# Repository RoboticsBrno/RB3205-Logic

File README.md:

# About Logic

Logic is a universal programmable toy designed for teaching programming
developed at [Robotárna](https://helceletka.cz/robotarna).

Logic resembles a game console. It has 105 RGB LEDs that can serve as a display, it
has numerous buttons and a buzzer. Under the hood, it is powered by the ESP32
microcontroller.

Kids (well, not only them) can create custom games and
learn programming while doing so. It is even possible to run multiplayer games as the on-board
processor features both, WiFi and Bluetooth 4.

This project was prepared for [Robotic Camp 2021](https://2021.robotickytabor.cz/) ­–
the page is available, however, in Czech. You will find more project there. You
can also see our [GitHub](https://github.com/RoboticsBrno) for find out more
about our other projects.

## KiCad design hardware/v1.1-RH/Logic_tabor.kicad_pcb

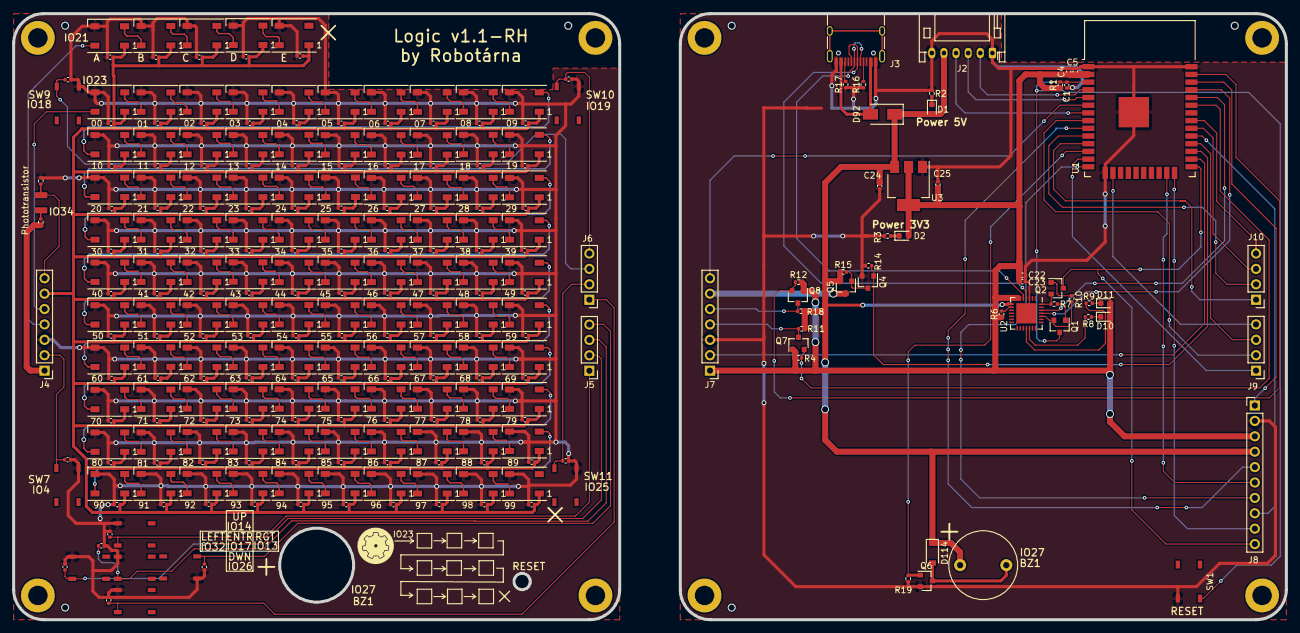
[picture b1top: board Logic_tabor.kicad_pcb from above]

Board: 2 copper layers, 100.0 x 100.0 mm, 294 parts (1 on the bottom side), 170 nets.

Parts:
B1, B2: Board
BZ1: Buzzer; PIEZO
C1: 1u; C_0402_1005Metric
C2, C3, C5, C6, C7, C8, C9, C10, C15, C16, C21, C23, C31, C32, C33, C34, C35, C36, C37, C38, C39, C40, C41, C42, C43, C44, C45, C46, C47, C48, C49, C50, C51, C52, C53, C54, C55, C56, C57, C58, C59, C60, C61, C62, C63, C64, C65, C66, C67, C68, C69, C70, C71, C72, C73, C74, C75, C76, C77, C78, C79, C80, C81, C82, C83, C84, C85, C86, C87, C88, C89, C90, C91, C92, C93, C94, C95, C96, C97, C98, C99, C100, C101, C102, C103, C104, C105, C106, C107, C108, C109, C110, C111, C112, C113, C114, C115, C116, C117, C118, C119, C120, C121, C122, C123, C124, C125: 100n; C_0402_1005Metric
C4, C22, C24, C25: 10u; C_0402_1005Metric
C11, C12, C13, C14, C17, C18, C19, C20, C126: 10n; C_0402_1005Metric
D1, D2, D10, D11: green; LED_0603_1608Metric
D3, D4, D5, D6, D12, D13, D14, D15, D16, D17, D18, D19, D20, D21, D22, D23, D24, D25, D26, D27, D28, D29, D30, D31, D32, D33, D34, D35, D36, D37, D38, D39, D40, D41, D42, D43, D44, D45, D46, D47, D48, D49, D50, D51, D52, D53, D54, D55, D56, D57, D58, D59, D60, D61, D62, D63, D64, D65, D66, D67, D68, D69, D70, D71, D72, D73, D74, D75, D76, D77, D78, D79, D80, D81, D82, D83, D84, D85, D86, D87, D88, D89, D90, D91, D93, D94, D95, D96, D97, D98, D99, D100, D101, D102, D103, D104, D105, D106, D107, D108, D109, D110, D111, D112, D113: WS2812C; LED_WS2812B_PLCC4_5.0x5.0mm_P3.2mm
D92: DIODE; D_SMA
D114: D_Schottky; D_SOD-123
DRA1, DRA2: Logo_Robotarna; RobotarnaLogo-6mm
H1, H2, H3, H4, H5, H6, H7, H8: MountingHole; MountingHole_3.2mm_M3_DIN965_Pad
J2: Conn_01x06_Male; JST_PH_S6B-PH-K_1x06_P2.00mm_Horizontal
J3: USB_C_Receptacle_USB2.0; USB_C_Receptacle_HRO_TYPE-C-31-M-12
J4: Conn_01x07_Female; PinHeader_1x07_P2.54mm_Vertical
J5, J6: Conn_01x04_Female; PinHeader_1x04_P2.54mm_Vertical
J7: Conn_01x07_Male; PinHeader_1x07_P2.54mm_Vertical
J8: Conn_01x10_Male; PinHeader_1x10_P2.54mm_Vertical
J9, J10: Conn_01x04_Male; PinHeader_1x04_P2.54mm_Vertical
Q1, Q2: Q_NPN_BEC; SOT-23
Q3: Q_Photo_NPN; SMD,3.5x2.8x1.9mm
Q4, Q6, Q7, Q8: Q_NMOS_GSD; SOT-23
Q5: Q_PMOS_GSD; SOT-23
R1, R2, R3, R4, R6, R7, R8, R9, R10, R11, R12, R13, R18: 10k; R_0402_1005Metric
R5: 22k; R_0402_1005Metric
R14, R15, R19: 100k; R_0402_1005Metric
R16, R17: 5k1; R_0402_1005Metric
SW1, SW2, SW3, SW4, SW5, SW7, SW8, SW9, SW10, SW11: button; Tactile_switch
U1: ESP32-WROOM-32
U2: CP2102N-A01-GQFN28; QFN-28-1EP_5x5mm_P0.5mm_EP3.35x3.35mm
U3: AMS1117-3.3; SOT-223-3_TabPin2

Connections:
5V: BZ1.1 (-), C24.1, D1.2 (A), D92.1 (K), D114.1 (K), J2.5, J8.4, Q5.2 (S), R11.1, R15.1, R18.1, U2.8 (VBUS), U3.3 (VI)
/elektronika.sch/3V3: C4.2, C5.2, C22.2, C23.2, C25.1, D2.2 (A), D10.2 (A), D11.2 (A), J7.1, J8.3, Q7.1 (G), Q8.1 (G), R1.1, R4.1, R6.1, R12.1, U1.2 (VDD), U2.6 (VDD), U2.7 (REGIN), U3.2 (VO)
/elektronika.sch/DATA_HERNI_LED: J7.5, Q8.3 (D), R18.2
/elektronika.sch/DATA_ZADANI_LED: J7.4, Q7.3 (D), R11.2
/elektronika.sch/GND: C1.2, C4.1, C5.1, C22.1, C23.1, C24.2, C25.2, J2.1, J2.6, J3.A1 (GND), J3.A12 (GND), J3.B1 (GND), J3.B12 (GND), J7.3, J8.2, Q4.2 (S), Q6.2 (S), R2.1, R3.1, R14.2, R16.1, R17.1, R19.1, SW1.2, U1.1 (GND), U1.15 (GND), U1.38 (GND), U1.39 (GND), U2.3 (GND), U2.29 (GND), U3.1 (GND)
/elektronika.sch/SENZOR_SVETLA: J7.7, U1.6 (IO34)
/elektronika.sch/SW_2: J9.3, U1.28 (IO17)
/elektronika.sch/SW_3: J9.4, U1.16 (IO13)
/elektronika.sch/SW_4: J9.2, U1.8 (IO32)
/elektronika.sch/SW_5: J9.1, U1.13 (IO14)
/elektronika.sch/SW_7: J7.2, U1.26 (IO4)
/elektronika.sch/SW_8: J10.1, U1.11 (IO26)
/elektronika.sch/SW_9: J10.3, U1.30 (IO18)
/elektronika.sch/SW_10: J10.4, U1.31 (IO19)
/elektronika.sch/SW_11: J10.2, U1.10 (IO25)
/elektronika.sch/V_LED_1: J7.6, Q5.3 (D)
/ovladaci_prvky.sch/3V3: J4.1, R5.1
/ovladaci_prvky.sch/DATA_HERNI_LED: D12.4 (DIN), J4.5
/ovladaci_prvky.sch/DATA_ZADANI_LED: D3.4 (DIN), J4.4
/ovladaci_prvky.sch/GND: C2.2, C3.2, C6.2, C7.2, C8.2, C9.2, C10.2, C11.1, C12.1, C13.1, C14.1, C15.2, C16.2, C17.1, C18.1, C19.1, C20.1, C21.2, C31.2, C32.2, C33.2, C34.2, C35.2, C36.2, C37.2, C38.2, C39.2, C40.2, C41.2, C42.2, C43.2, C44.2, C45.2, C46.2, C47.2, C48.2, C49.2, C50.2, C51.2, C52.2, C53.2, C54.2, C55.2, C56.2, C57.2, C58.2, C59.2, C60.2, C61.2, C62.2, C63.2, C64.2, C65.2, C66.2, C67.2, C68.2, C69.2, C70.2, C71.2, C72.2, C73.2, C74.2, C75.2, C76.2, C77.2, C78.2, C79.2, C80.2, C81.2, C82.2, C83.2, C84.2, C85.2, C86.2, C87.2, C88.2, C89.2, C90.2, C91.2, C92.2, C93.2, C94.2, C95.2, C96.2, C97.2, C98.2, C99.2, C100.2, C101.2, C102.2, C103.2, C104.2, C105.2, C106.2, C107.2, C108.2, C109.2, C110.2, C111.2, C112.2, C113.2, C114.2, C115.2, C116.2, C117.2, C118.2, C119.2, C120.2, C121.2, C122.2, C123.2, C124.2, C125.2, C126.1, D3.3 (VSS), D4.3 (VSS), D5.3 (VSS), D6.3 (VSS), D12.3 (VSS), D13.3 (VSS), D14.3 (VSS), D15.3 (VSS), D16.3 (VSS), D17.3 (VSS), D18.3 (VSS), D19.3 (VSS), D20.3 (VSS), D21.3 (VSS), D22.3 (VSS), D23.3 (VSS), D24.3 (VSS), D25.3 (VSS), D26.3 (VSS), D27.3 (VSS), D28.3 (VSS), D29.3 (VSS), D30.3 (VSS), D31.3 (VSS), D32.3 (VSS), D33.3 (VSS), D34.3 (VSS), D35.3 (VSS), D36.3 (VSS), D37.3 (VSS), D38.3 (VSS), D39.3 (VSS), D40.3 (VSS), D41.3 (VSS), D42.3 (VSS), D43.3 (VSS), D44.3 (VSS), D45.3 (VSS), D46.3 (VSS), D47.3 (VSS), D48.3 (VSS), D49.3 (VSS), D50.3 (VSS), D51.3 (VSS), D52.3 (VSS), D53.3 (VSS), D54.3 (VSS), D55.3 (VSS), D56.3 (VSS), D57.3 (VSS), D58.3 (VSS), D59.3 (VSS), D60.3 (VSS), D61.3 (VSS), D62.3 (VSS), D63.3 (VSS), D64.3 (VSS), D65.3 (VSS), D66.3 (VSS), D67.3 (VSS), D68.3 (VSS), D69.3 (VSS), D70.3 (VSS), D71.3 (VSS), D72.3 (VSS), D73.3 (VSS), D74.3 (VSS), D75.3 (VSS), D76.3 (VSS), D77.3 (VSS), D78.3 (VSS), D79.3 (VSS), D80.3 (VSS), D81.3 (VSS), D82.3 (VSS), D83.3 (VSS), D84.3 (VSS), D85.3 (VSS), D86.3 (VSS), D87.3 (VSS), D88.3 (VSS), D89.3 (VSS), D90.3 (VSS), D91.3 (VSS), D93.3 (VSS), D94.3 (VSS), D95.3 (VSS), D96.3 (VSS), D97.3 (VSS), D98.3 (VSS), D99.3 (VSS), D100.3 (VSS), D101.3 (VSS), D102.3 (VSS), D103.3 (VSS), D104.3 (VSS), D105.3 (VSS), D106.3 (VSS), D107.3 (VSS), D108.3 (VSS), D109.3 (VSS), D110.3 (VSS), D111.3 (VSS), D112.3 (VSS), D113.3 (VSS), J4.3, R13.2, SW2.2, SW3.2, SW4.2, SW5.2, SW7.2, SW8.2, SW9.2, SW10.2, SW11.2
/ovladaci_prvky.sch/SENZOR_SVETLA: J4.7, Q3.2 (E), R13.1
/ovladaci_prvky.sch/SW_2: C11.2, J5.3, SW2.1
/ovladaci_prvky.sch/SW_3: C12.2, J5.4, SW3.1
/ovladaci_prvky.sch/SW_4: C13.2, J5.2, SW4.1
/ovladaci_prvky.sch/SW_5: C14.2, J5.1, SW5.1
/ovladaci_prvky.sch/SW_7: C126.2, J4.2, SW7.1
/ovladaci_prvky.sch/SW_8: C17.2, J6.1, SW8.1
/ovladaci_prvky.sch/SW_9: C18.2, J6.3, SW9.1
/ovladaci_prvky.sch/SW_10: C19.2, J6.4, SW10.1
/ovladaci_prvky.sch/SW_11: C20.2, J6.2, SW11.1
/ovladaci_prvky.sch/V_LED_1: C2.1, C3.1, C6.1, C7.1, C8.1, C9.1, C10.1, C15.1, C16.1, C21.1, C31.1, C32.1, C33.1, C34.1, C35.1, C36.1, C37.1, C38.1, C39.1, C40.1, C41.1, C42.1, C43.1, C44.1, C45.1, C46.1, C47.1, C48.1, C49.1, C50.1, C51.1, C52.1, C53.1, C54.1, C55.1, C56.1, C57.1, C58.1, C59.1, C60.1, C61.1, C62.1, C63.1, C64.1, C65.1, C66.1, C67.1, C68.1, C69.1, C70.1, C71.1, C72.1, C73.1, C74.1, C75.1, C76.1, C77.1, C78.1, C79.1, C80.1, C81.1, C82.1, C83.1, C84.1, C85.1, C86.1, C87.1, C88.1, C89.1, C90.1, C91.1, C92.1, C93.1, C94.1, C95.1, C96.1, C97.1, C98.1, C99.1, C100.1, C101.1, C102.1, C103.1, C104.1, C105.1, C106.1, C107.1, C108.1, C109.1, C110.1, C111.1, C112.1, C113.1, C114.1, C115.1, C116.1, C117.1, C118.1, C119.1, C120.1, C121.1, C122.1, C123.1, C124.1, C125.1, D3.1 (VDD), D4.1 (VDD), D5.1 (VDD), D6.1 (VDD), D12.1 (VDD), D13.1 (VDD), D14.1 (VDD), D15.1 (VDD), D16.1 (VDD), D17.1 (VDD), D18.1 (VDD), D19.1 (VDD), D20.1 (VDD), D21.1 (VDD), D22.1 (VDD), D23.1 (VDD), D24.1 (VDD), D25.1 (VDD), D26.1 (VDD), D27.1 (VDD), D28.1 (VDD), D29.1 (VDD), D30.1 (VDD), D31.1 (VDD), D32.1 (VDD), D33.1 (VDD), D34.1 (VDD), D35.1 (VDD), D36.1 (VDD), D37.1 (VDD), D38.1 (VDD), D39.1 (VDD), D40.1 (VDD), D41.1 (VDD), D42.1 (VDD), D43.1 (VDD), D44.1 (VDD), D45.1 (VDD), D46.1 (VDD), D47.1 (VDD), D48.1 (VDD), D49.1 (VDD), D50.1 (VDD), D51.1 (VDD), D52.1 (VDD), D53.1 (VDD), D54.1 (VDD), D55.1 (VDD), D56.1 (VDD), D57.1 (VDD), D58.1 (VDD), D59.1 (VDD), D60.1 (VDD), D61.1 (VDD), D62.1 (VDD), D63.1 (VDD), D64.1 (VDD), D65.1 (VDD), D66.1 (VDD), D67.1 (VDD), D68.1 (VDD), D69.1 (VDD), D70.1 (VDD), D71.1 (VDD), D72.1 (VDD), D73.1 (VDD), D74.1 (VDD), D75.1 (VDD), D76.1 (VDD), D77.1 (VDD), D78.1 (VDD), D79.1 (VDD), D80.1 (VDD), D81.1 (VDD), D82.1 (VDD), D83.1 (VDD), D84.1 (VDD), D85.1 (VDD), D86.1 (VDD), D87.1 (VDD), D88.1 (VDD), D89.1 (VDD), D90.1 (VDD), D91.1 (VDD), D93.1 (VDD), D94.1 (VDD), D95.1 (VDD), D96.1 (VDD), D97.1 (VDD), D98.1 (VDD), D99.1 (VDD), D100.1 (VDD), D101.1 (VDD), D102.1 (VDD), D103.1 (VDD), D104.1 (VDD), D105.1 (VDD), D106.1 (VDD), D107.1 (VDD), D108.1 (VDD), D109.1 (VDD), D110.1 (VDD), D111.1 (VDD), D112.1 (VDD), D113.1 (VDD), J4.6
/ovladaci_prvky.sch/herni_pole_LED.sch/1.sch/DATA_OUT: D16.2 (DOUT), D17.4 (DIN)
/ovladaci_prvky.sch/herni_pole_LED.sch/2.sch/DATA_OUT: D21.2 (DOUT), D22.4 (DIN)
/ovladaci_prvky.sch/herni_pole_LED.sch/3.sch/DATA_OUT: D26.2 (DOUT), D27.4 (DIN)
/ovladaci_prvky.sch/herni_pole_LED.sch/4.sch/DATA_OUT: D31.2 (DOUT), D32.4 (DIN)
/ovladaci_prvky.sch/herni_pole_LED.sch/5.sch/DATA_OUT: D36.2 (DOUT), D37.4 (DIN)
/ovladaci_prvky.sch/herni_pole_LED.sch/6.sch/DATA_OUT: D41.2 (DOUT), D42.4 (DIN)
/ovladaci_prvky.sch/herni_pole_LED.sch/7.sch/DATA_OUT: D46.2 (DOUT), D47.4 (DIN)
/ovladaci_prvky.sch/herni_pole_LED.sch/8.sch/DATA_OUT: D51.2 (DOUT), D52.4 (DIN)
/ovladaci_prvky.sch/herni_pole_LED.sch/10.sch/DATA_IN: D56.2 (DOUT), D57.4 (DIN)
/ovladaci_prvky.sch/herni_pole_LED.sch/10.sch/DATA_OUT: D61.2 (DOUT), D62.4 (DIN)
/ovladaci_prvky.sch/herni_pole_LED.sch/11.sch/DATA_OUT: D66.2 (DOUT), D67.4 (DIN)
/ovladaci_prvky.sch/herni_pole_LED.sch/12.sch/DATA_OUT: D71.2 (DOUT), D72.4 (DIN)
/ovladaci_prvky.sch/herni_pole_LED.sch/13.sch/DATA_OUT: D76.2 (DOUT), D77.4 (DIN)
/ovladaci_prvky.sch/herni_pole_LED.sch/14.sch/DATA_OUT: D81.2 (DOUT), D82.4 (DIN)
/ovladaci_prvky.sch/herni_pole_LED.sch/15.sch/DATA_OUT: D86.2 (DOUT), D87.4 (DIN)
/ovladaci_prvky.sch/herni_pole_LED.sch/16.sch/DATA_OUT: D91.2 (DOUT), D93.4 (DIN)
/ovladaci_prvky.sch/herni_pole_LED.sch/17.sch/DATA_OUT: D97.2 (DOUT), D98.4 (DIN)
/ovladaci_prvky.sch/herni_pole_LED.sch/18.sch/DATA_OUT: D102.2 (DOUT), D103.4 (DIN)
/ovladaci_prvky.sch/herni_pole_LED.sch/19.sch/DATA_OUT: D107.2 (DOUT), D108.4 (DIN)
DATA_HERNI_LED_LS: Q8.2 (S), R12.2, U1.37 (IO23)
DATA_ZADANI_LED_LS: Q7.2 (S), R4.2, U1.33 (IO21)
EN: C1.1, Q1.3 (C), R1.2, SW1.1, U1.3 (EN)
IO0: J8.10, Q2.3 (C), U1.25 (IO0)
IO2: J8.9, U1.24 (IO2)
IO5: J8.8, U1.29 (IO5)
IO12: J8.7, U1.14 (IO12)
IO15: J8.6, U1.23 (IO15)
IO22: J8.1, U1.36 (IO22)
IO33: J8.5, U1.9 (IO33)
unnamed: BZ1.2 (+), D114.2 (A), Q6.3 (D)
unnamed: D1.1 (K), R2.2
unnamed: D2.1 (K), R3.2
unnamed: D3.2 (DOUT), D4.4 (DIN)
unnamed: D4.2 (DOUT), D5.4 (DIN)
unnamed: D5.2 (DOUT), D6.4 (DIN)
unnamed: D10.1 (K), R8.1
unnamed: D11.1 (K), R9.1
unnamed: D12.2 (DOUT), D13.4 (DIN)
unnamed: D13.2 (DOUT), D14.4 (DIN)
unnamed: D14.2 (DOUT), D15.4 (DIN)
unnamed: D15.2 (DOUT), D16.4 (DIN)
unnamed: D17.2 (DOUT), D18.4 (DIN)
unnamed: D18.2 (DOUT), D19.4 (DIN)
unnamed: D19.2 (DOUT), D20.4 (DIN)
unnamed: D20.2 (DOUT), D21.4 (DIN)
unnamed: D22.2 (DOUT), D23.4 (DIN)
unnamed: D23.2 (DOUT), D24.4 (DIN)
unnamed: D24.2 (DOUT), D25.4 (DIN)
unnamed: D25.2 (DOUT), D26.4 (DIN)
unnamed: D27.2 (DOUT), D28.4 (DIN)
unnamed: D28.2 (DOUT), D29.4 (DIN)
unnamed: D29.2 (DOUT), D30.4 (DIN)
unnamed: D30.2 (DOUT), D31.4 (DIN)
unnamed: D32.2 (DOUT), D33.4 (DIN)
unnamed: D33.2 (DOUT), D34.4 (DIN)
unnamed: D34.2 (DOUT), D35.4 (DIN)
unnamed: D35.2 (DOUT), D36.4 (DIN)
unnamed: D37.2 (DOUT), D38.4 (DIN)
unnamed: D38.2 (DOUT), D39.4 (DIN)
unnamed: D39.2 (DOUT), D40.4 (DIN)
unnamed: D40.2 (DOUT), D41.4 (DIN)
unnamed: D42.2 (DOUT), D43.4 (DIN)
unnamed: D43.2 (DOUT), D44.4 (DIN)
unnamed: D44.2 (DOUT), D45.4 (DIN)
unnamed: D45.2 (DOUT), D46.4 (DIN)
unnamed: D47.2 (DOUT), D48.4 (DIN)
unnamed: D48.2 (DOUT), D49.4 (DIN)
unnamed: D49.2 (DOUT), D50.4 (DIN)
unnamed: D50.2 (DOUT), D51.4 (DIN)
unnamed: D52.2 (DOUT), D53.4 (DIN)
unnamed: D53.2 (DOUT), D54.4 (DIN)
unnamed: D54.2 (DOUT), D55.4 (DIN)
unnamed: D55.2 (DOUT), D56.4 (DIN)
unnamed: D57.2 (DOUT), D58.4 (DIN)
unnamed: D58.2 (DOUT), D59.4 (DIN)
unnamed: D59.2 (DOUT), D60.4 (DIN)
unnamed: D60.2 (DOUT), D61.4 (DIN)
unnamed: D62.2 (DOUT), D63.4 (DIN)
unnamed: D63.2 (DOUT), D64.4 (DIN)
unnamed: D64.2 (DOUT), D65.4 (DIN)
unnamed: D65.2 (DOUT), D66.4 (DIN)
unnamed: D67.2 (DOUT), D68.4 (DIN)
unnamed: D68.2 (DOUT), D69.4 (DIN)
unnamed: D69.2 (DOUT), D70.4 (DIN)
unnamed: D70.2 (DOUT), D71.4 (DIN)
unnamed: D72.2 (DOUT), D73.4 (DIN)
unnamed: D73.2 (DOUT), D74.4 (DIN)
unnamed: D74.2 (DOUT), D75.4 (DIN)
unnamed: D75.2 (DOUT), D76.4 (DIN)
unnamed: D77.2 (DOUT), D78.4 (DIN)
unnamed: D78.2 (DOUT), D79.4 (DIN)
unnamed: D79.2 (DOUT), D80.4 (DIN)
unnamed: D80.2 (DOUT), D81.4 (DIN)
unnamed: D82.2 (DOUT), D83.4 (DIN)
unnamed: D83.2 (DOUT), D84.4 (DIN)
unnamed: D84.2 (DOUT), D85.4 (DIN)
unnamed: D85.2 (DOUT), D86.4 (DIN)
unnamed: D87.2 (DOUT), D88.4 (DIN)
unnamed: D88.2 (DOUT), D89.4 (DIN)
unnamed: D89.2 (DOUT), D90.4 (DIN)
unnamed: D90.2 (DOUT), D91.4 (DIN)
unnamed: D92.2 (A), J3.A4 (VBUS), J3.A9 (VBUS), J3.B4 (VBUS), J3.B9 (VBUS)
unnamed: D93.2 (DOUT), D94.4 (DIN)
unnamed: D94.2 (DOUT), D95.4 (DIN)
unnamed: D95.2 (DOUT), D96.4 (DIN)
unnamed: D96.2 (DOUT), D97.4 (DIN)
unnamed: D98.2 (DOUT), D99.4 (DIN)
unnamed: D100.2 (DOUT), D101.4 (DIN)
unnamed: D99.2 (DOUT), D100.4 (DIN)
unnamed: D101.2 (DOUT), D102.4 (DIN)
unnamed: D103.2 (DOUT), D104.4 (DIN)
unnamed: D104.2 (DOUT), D105.4 (DIN)
unnamed: D105.2 (DOUT), D106.4 (DIN)
unnamed: D106.2 (DOUT), D107.4 (DIN)
unnamed: D108.2 (DOUT), D109.4 (DIN)
unnamed: D109.2 (DOUT), D110.4 (DIN)
unnamed: D110.2 (DOUT), D111.4 (DIN)
unnamed: D111.2 (DOUT), D112.4 (DIN)
unnamed: D6.2 (DOUT), D113.4 (DIN)
unnamed: J3.A5 (CC1), R16.2
unnamed: J3.A6 (D+), J3.B6 (D+), U2.4 (D+)
unnamed: J3.A7 (D-), J3.B7 (D-), U2.5 (D-)
unnamed: J3.B5 (CC2), R17.2
unnamed: Q1.1 (B), R7.1
unnamed: Q1.2 (E), R10.2, U2.24 (~RTS)
unnamed: Q2.1 (B), R10.1
unnamed: Q2.2 (E), R7.2, U2.28 (~DTR)
unnamed: Q3.1 (C), R5.2
unnamed: Q4.3 (D), Q5.1 (G), R15.2
unnamed: R6.2, U2.9 (~RSTb)
unnamed: R8.2, U2.19 (~TXT/GPIO.0)
unnamed: R9.2, U2.18 (~RXT/GPIO.1)
PIEZO: Q6.1 (G), R19.2, U1.12 (IO27)
RX_ESP: U1.34 (RXD0/IO3), U2.26 (TXD)
TX_ESP: U1.35 (TXD0/IO1), U2.25 (RXD)
VSTUP1: J2.3, U1.5 (SENSOR_VN)
VSTUP2: J2.2, U1.4 (SENSOR_VP)
VSTUP3: J2.4, U1.7 (IO35)
ZAPINANI_1_CAST_LED: Q4.1 (G), R14.1, U1.27 (IO16)

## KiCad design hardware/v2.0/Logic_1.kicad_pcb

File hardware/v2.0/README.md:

# About Logic

## changes compared to V1.1:
- ESP32-S3
- SD card

<div align="center">
    
</div>

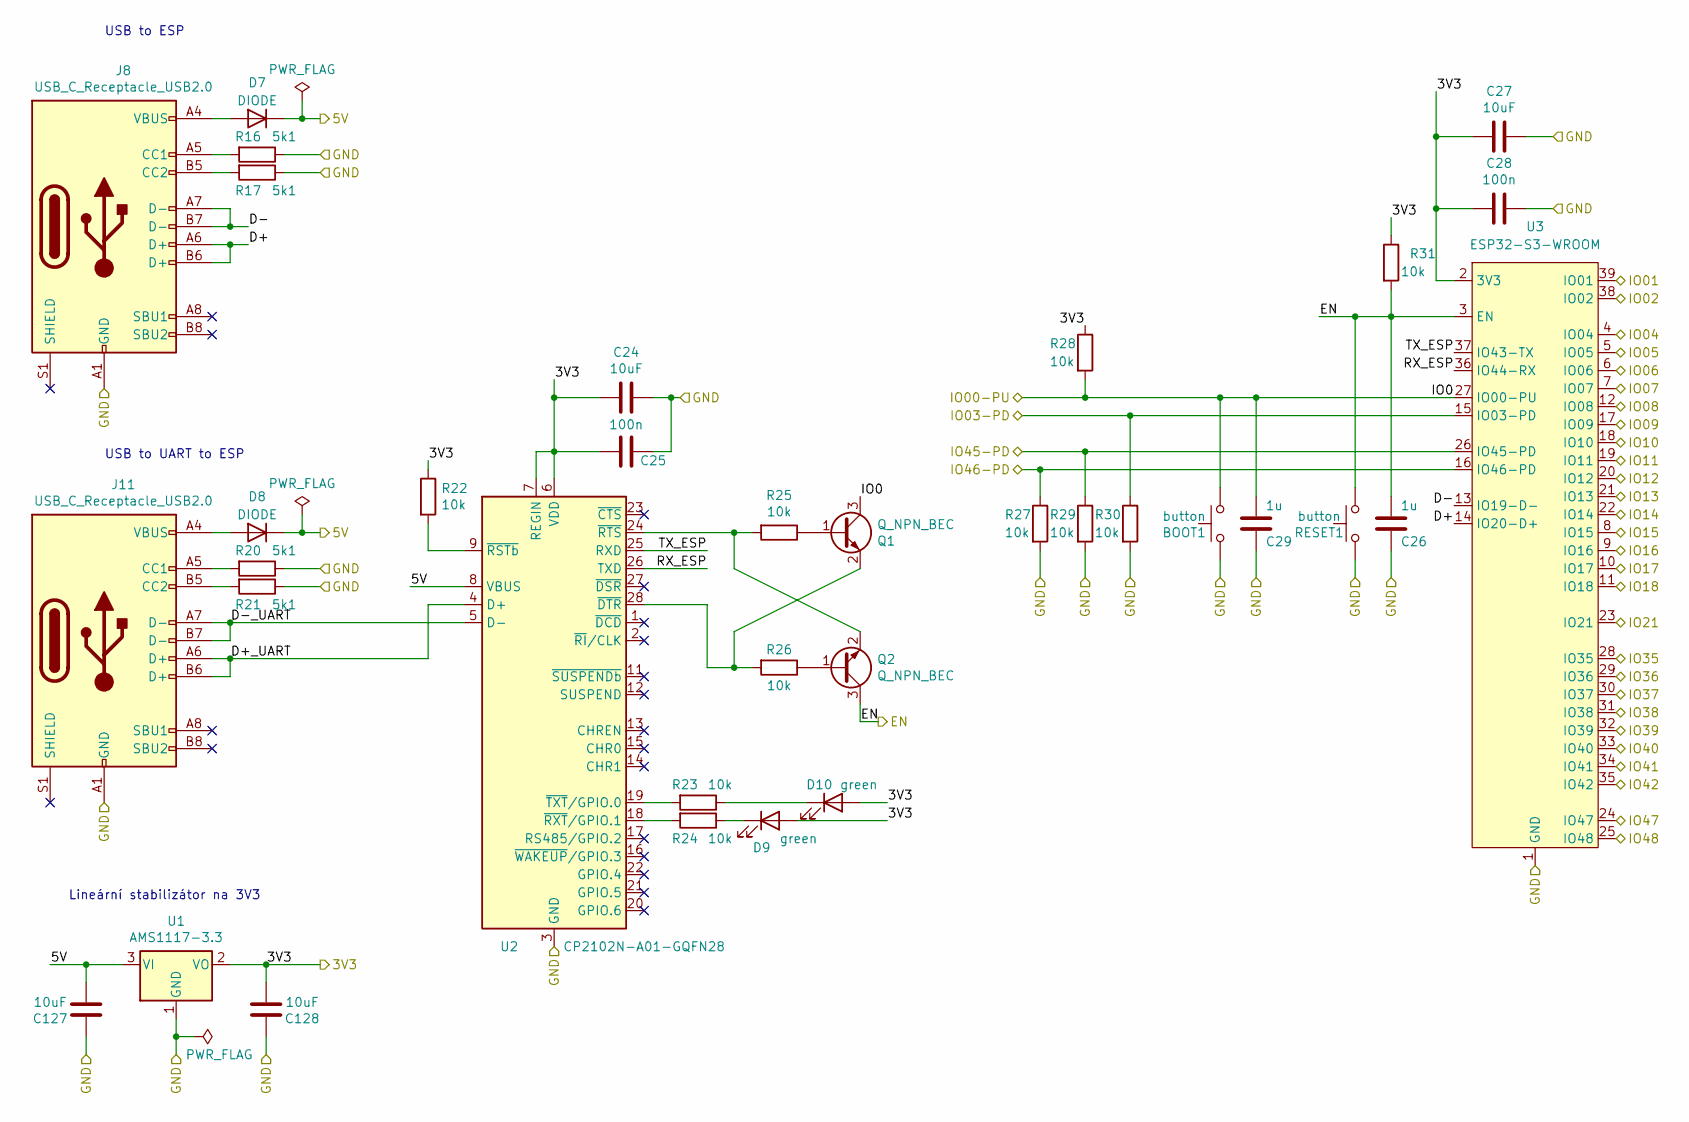
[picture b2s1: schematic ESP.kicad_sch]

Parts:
BOOT1: button; Tactile_switch; LCSC C318887
C24, C27, C127, C128: 10uF; C_0603_1608Metric; LCSC C96446
C25, C28: 100n; C_0402_1005Metric; LCSC C1525
C26, C29: 1u; C_0402_1005Metric; LCSC C52923
D7, D8: DIODE; D_SMA; LCSC C8678
D9, D10: green; LED_0603_1608Metric; LCSC C72043
J8, J11: USB_C_Receptacle_USB2.0; USB_C_Receptacle_HRO_TYPE-C-31-M-12; LCSC C165948
Q1, Q2: Q_NPN_BEC; SOT-23; LCSC C20526
R16, R17, R20, R21: 5k1; R_0402_1005Metric; JLCPCB_CORRECTION 0;0;0
R22, R23, R24, R25, R26, R27, R28, R29, R30, R31: 10k; R_0402_1005Metric; LCSC C25744
RESET1: button; Tactile_switch; LCSC C318887
U1: AMS1117-3.3; SOT-223-3_TabPin2; JLCPCB_CORRECTION 0;0;180
U2: CP2102N-A01-GQFN28; QFN-28-1EP_5x5mm_P0.5mm_EP3.35x3.35mm; LCSC C6568
U3: ESP32-S3-WROOM; LCSC C2913199

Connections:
/elektronika.sch/3V3: C24.2, C25.2, C27.2, C28.2, C128.1, D9.2 (A), D10.2 (A), R22.1, R28.1, R31.1, U1.2 (VO), U2.6 (VDD), U2.7 (REGIN), U3.2 (3V3); also elsewhere on the board
/elektronika.sch/5V: C127.1, D7.1 (K), D8.1 (K), U1.3 (VI), U2.8 (VBUS); also elsewhere on the board
/elektronika.sch/DATA_HERNI_LED_LS: R29.1, U3.26 (IO45-PD); also elsewhere on the board
/elektronika.sch/DATA_ZADANI_LED_LS: R27.1, U3.16 (IO46-PD); also elsewhere on the board
/elektronika.sch/EN: C26.1, Q2.3 (C), R31.2, RESET1.1, U3.3 (EN); also elsewhere on the board
/elektronika.sch/ESP+programing/D+: J8.A6 (D+), J8.B6 (D+), U3.14 (IO20-D+)
/elektronika.sch/ESP+programing/D+_UART: J11.A6 (D+), J11.B6 (D+), U2.4 (D+)
/elektronika.sch/ESP+programing/D-: J8.A7 (D-), J8.B7 (D-), U3.13 (IO19-D-)
/elektronika.sch/ESP+programing/D-_UART: J11.A7 (D-), J11.B7 (D-), U2.5 (D-)
/elektronika.sch/ESP+programing/IO03-PD: R30.1, U3.15 (IO03-PD); also elsewhere on the board
/elektronika.sch/ESP+programing/IO11: U3.19 (IO11); also elsewhere on the board
/elektronika.sch/ESP+programing/IO12: U3.20 (IO12); also elsewhere on the board
/elektronika.sch/ESP+programing/IO13: U3.21 (IO13); also elsewhere on the board
/elektronika.sch/ESP+programing/IO48: U3.25 (IO48); also elsewhere on the board
/elektronika.sch/ESP+programing/RX_ESP: U2.26 (TXD), U3.36 (IO44-RX)
/elektronika.sch/ESP+programing/TX_ESP: U2.25 (RXD), U3.37 (IO43-TX)
/elektronika.sch/GND: BOOT1.2, C24.1, C25.1, C26.2, C27.1, C28.1, C29.2, C127.2, C128.2, J8.A1 (GND), J8.A12 (GND), J8.B1 (GND), J8.B12 (GND), J11.A1 (GND), J11.A12 (GND), J11.B1 (GND), J11.B12 (GND), R16.1, R17.1, R20.1, R21.1, R27.2, R29.2, R30.2, RESET1.2, U1.1 (GND), U2.3 (GND), U2.29 (GND), U3.1 (GND), U3.40 (GND), U3.41 (GND); also elsewhere on the board
/elektronika.sch/IO15: U3.8 (IO15); also elsewhere on the board
/elektronika.sch/IO16: U3.9 (IO16); also elsewhere on the board
/elektronika.sch/IO17: U3.10 (IO17); also elsewhere on the board
/elektronika.sch/IO18: U3.11 (IO18); also elsewhere on the board
/elektronika.sch/IO35: U3.28 (IO35); also elsewhere on the board
/elektronika.sch/IO36: U3.29 (IO36); also elsewhere on the board
/elektronika.sch/IO37: U3.30 (IO37); also elsewhere on the board
/elektronika.sch/IO38: U3.31 (IO38); also elsewhere on the board
/elektronika.sch/IO39: U3.32 (IO39); also elsewhere on the board
/elektronika.sch/IO40: U3.33 (IO40); also elsewhere on the board
/elektronika.sch/IO41: U3.34 (IO41); also elsewhere on the board
/elektronika.sch/IO42: U3.35 (IO42); also elsewhere on the board
/elektronika.sch/PIEZO: U3.23 (IO21); also elsewhere on the board
/elektronika.sch/SENZOR_SVETLA: U3.38 (IO02); also elsewhere on the board
/elektronika.sch/SW_2: U3.5 (IO05); also elsewhere on the board
/elektronika.sch/SW_3: U3.6 (IO06); also elsewhere on the board
/elektronika.sch/SW_4: U3.18 (IO10); also elsewhere on the board
/elektronika.sch/SW_5: U3.4 (IO04); also elsewhere on the board
/elektronika.sch/SW_7: U3.39 (IO01); also elsewhere on the board
/elektronika.sch/SW_8: U3.7 (IO07); also elsewhere on the board
/elektronika.sch/SW_9: U3.22 (IO14); also elsewhere on the board
/elektronika.sch/SW_10: U3.17 (IO09); also elsewhere on the board
/elektronika.sch/SW_11: U3.12 (IO08); also elsewhere on the board
/elektronika.sch/SW_12: U3.24 (IO47); also elsewhere on the board
/elektronika.sch/ZAPINANI_1_CAST_LED: BOOT1.1, C29.1, Q1.3 (C), R28.2, U3.27 (IO00-PU); also elsewhere on the board
unnamed: D7.2 (A), J8.A4 (VBUS), J8.A9 (VBUS), J8.B4 (VBUS), J8.B9 (VBUS)
unnamed: D8.2 (A), J11.A4 (VBUS), J11.A9 (VBUS), J11.B4 (VBUS), J11.B9 (VBUS)
unnamed: D9.1 (K), R24.1
unnamed: D10.1 (K), R23.1
unnamed: J8.A5 (CC1), R16.2
unnamed: J8.B5 (CC2), R17.2
unnamed: J11.A5 (CC1), R20.2
unnamed: J11.B5 (CC2), R21.2
unnamed: Q1.1 (B), R25.1
unnamed: Q1.2 (E), R26.2, U2.28 (~DTR)
unnamed: Q2.1 (B), R26.1
unnamed: Q2.2 (E), R25.2, U2.24 (~RTS)
unnamed: R22.2, U2.9 (~RSTb)
unnamed: R23.2, U2.19 (~TXT/GPIO.0)
unnamed: R24.2, U2.18 (~RXT/GPIO.1)

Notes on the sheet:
USB to UART to ESP
Lineární stabilizátor na 3V3
USB to ESP

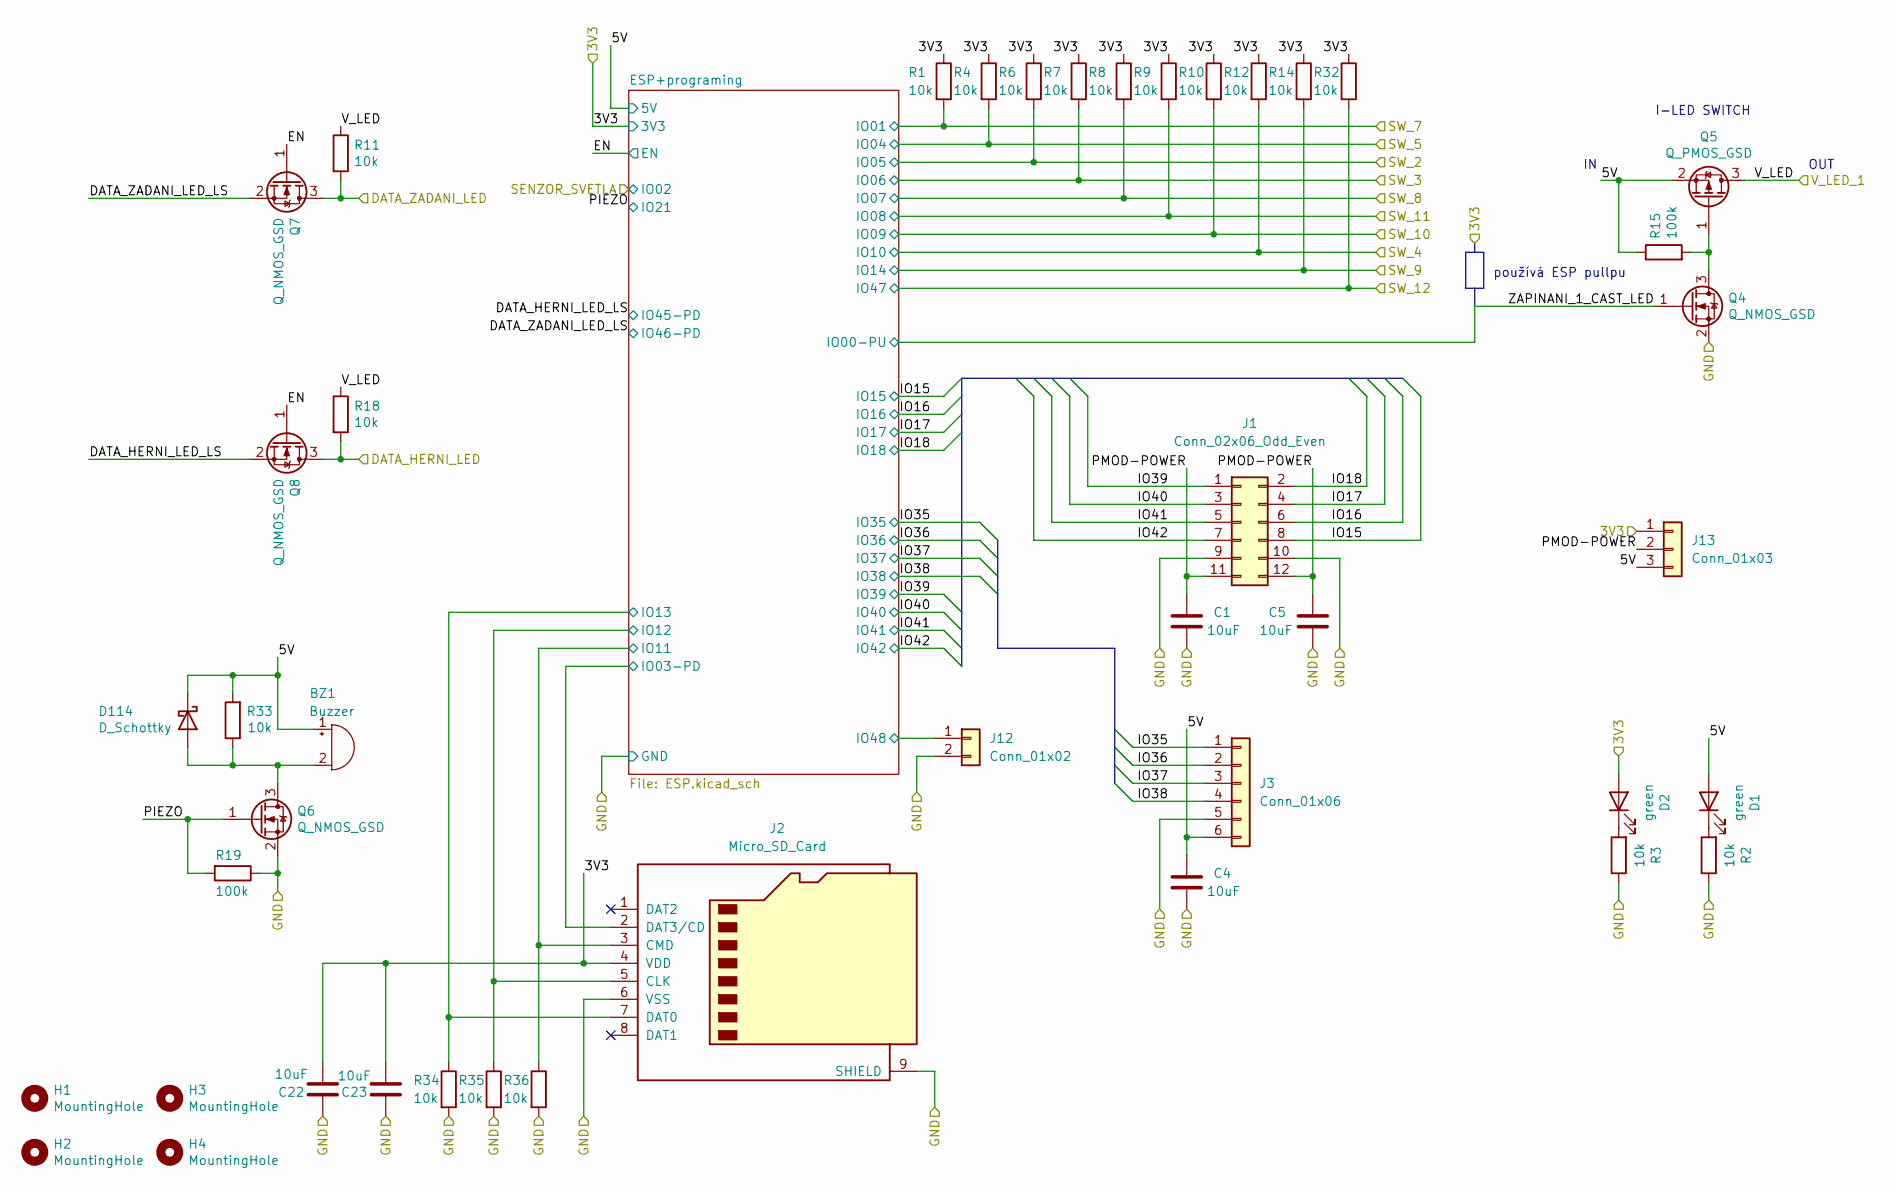
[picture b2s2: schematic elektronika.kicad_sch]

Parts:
BZ1: Buzzer; PKLCS1212E-(RH-Logic_piezzo); LCSC C113159
C1, C4, C5, C22, C23: 10uF; C_0603_1608Metric; LCSC C96446
D1, D2: green; LED_0603_1608Metric; LCSC C72043
D114: D_Schottky; D_SOD-123; JLCPCB_CORRECTION 0;0;0
H1, H2, H3, H4: MountingHole; MountingHole_3.2mm_M3_DIN965_Pad; JLCPCB_CORRECTION 0;0;0
J1: Conn_02x06_Odd_Even; PinSocket_2x06_P2.54mm_Horizontal; LCSC C2897426
J2: Micro_SD_Card; TF-01A; LCSC C91145
J3: Conn_01x06; PinSocket_1x06_P2.54mm_Horizontal; JLCPCB_IGNORE 1
J12: Conn_01x02; PinSocket_1x02_P2.54mm_Vertical; JLCPCB_IGNORE 1
J13: Conn_01x03; PinHeader_1x03_P2.54mm_Horizontal; LCSC C2935928
Q4, Q6, Q7, Q8: Q_NMOS_GSD; SOT-23; LCSC C8545
Q5: Q_PMOS_GSD; SOT-23; LCSC C15127
R1, R2, R3, R4, R6, R7, R8, R9, R10, R11, R12, R14, R18, R32, R33, R34, R35, R36: 10k; R_0402_1005Metric; LCSC C25744
R15, R19: 100k; R_0402_1005Metric; LCSC C25741

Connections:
/elektronika.sch/3V3: C22.1, C23.1, D2.2 (A), J2.4 (VDD), J13.1, R1.1, R4.1, R6.1, R7.1, R8.1, R9.1, R10.1, R12.1, R14.1, R32.1; also elsewhere on the board
/elektronika.sch/5V: BZ1.1 (-), C4.1, D1.2 (A), D114.1 (K), J3.6, J13.3, Q5.2 (S), R15.1, R33.2; also elsewhere on the board
/elektronika.sch/DATA_HERNI_LED: Q8.3 (D), R18.2; also elsewhere on the board
/elektronika.sch/DATA_HERNI_LED_LS: Q8.2 (S); also elsewhere on the board
/elektronika.sch/DATA_ZADANI_LED: Q7.3 (D), R11.2; also elsewhere on the board
/elektronika.sch/DATA_ZADANI_LED_LS: Q7.2 (S); also elsewhere on the board
/elektronika.sch/EN: Q7.1 (G), Q8.1 (G); also elsewhere on the board
/elektronika.sch/ESP+programing/IO03-PD: J2.2 (DAT3/CD); also elsewhere on the board
/elektronika.sch/ESP+programing/IO11: J2.3 (CMD), R36.1; also elsewhere on the board
/elektronika.sch/ESP+programing/IO12: J2.5 (CLK), R35.1; also elsewhere on the board
/elektronika.sch/ESP+programing/IO13: J2.7 (DAT0), R34.1; also elsewhere on the board
/elektronika.sch/ESP+programing/IO48: J12.1; also elsewhere on the board
/elektronika.sch/GND: C1.2, C4.2, C5.2, C22.2, C23.2, J1.9, J1.10, J2.6 (VSS), J2.9 (SHIELD), J3.5, J12.2, Q4.2 (S), Q6.2 (S), R2.1, R3.1, R19.1, R34.2, R35.2, R36.2; also elsewhere on the board
/elektronika.sch/IO15: J1.8; also elsewhere on the board
/elektronika.sch/IO16: J1.6; also elsewhere on the board
/elektronika.sch/IO17: J1.4; also elsewhere on the board
/elektronika.sch/IO18: J1.2; also elsewhere on the board
/elektronika.sch/IO35: J3.1; also elsewhere on the board
/elektronika.sch/IO36: J3.2; also elsewhere on the board
/elektronika.sch/IO37: J3.3; also elsewhere on the board
/elektronika.sch/IO38: J3.4; also elsewhere on the board
/elektronika.sch/IO39: J1.1; also elsewhere on the board
/elektronika.sch/IO40: J1.3; also elsewhere on the board
/elektronika.sch/IO41: J1.5; also elsewhere on the board
/elektronika.sch/IO42: J1.7; also elsewhere on the board
/elektronika.sch/PIEZO: Q6.1 (G), R19.2; also elsewhere on the board
/elektronika.sch/PMOD-POWER: C1.1, C5.1, J1.11, J1.12, J13.2
/elektronika.sch/SW_2: R6.2; also elsewhere on the board
/elektronika.sch/SW_3: R7.2; also elsewhere on the board
/elektronika.sch/SW_4: R12.2; also elsewhere on the board
/elektronika.sch/SW_5: R4.2; also elsewhere on the board
/elektronika.sch/SW_7: R1.2; also elsewhere on the board
/elektronika.sch/SW_8: R8.2; also elsewhere on the board
/elektronika.sch/SW_9: R14.2; also elsewhere on the board
/elektronika.sch/SW_10: R10.2; also elsewhere on the board
/elektronika.sch/SW_11: R9.2; also elsewhere on the board
/elektronika.sch/SW_12: R32.2; also elsewhere on the board
/elektronika.sch/V_LED: Q5.3 (D), R11.1, R18.1; also elsewhere on the board
/elektronika.sch/ZAPINANI_1_CAST_LED: Q4.1 (G); also elsewhere on the board
unnamed: BZ1.2 (+), D114.2 (A), Q6.3 (D), R33.1
unnamed: D1.1 (K), R2.2
unnamed: D2.1 (K), R3.2
unnamed: Q4.3 (D), Q5.1 (G), R15.2

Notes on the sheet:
používá ESP pullpu
I-LED SWITCH
OUT

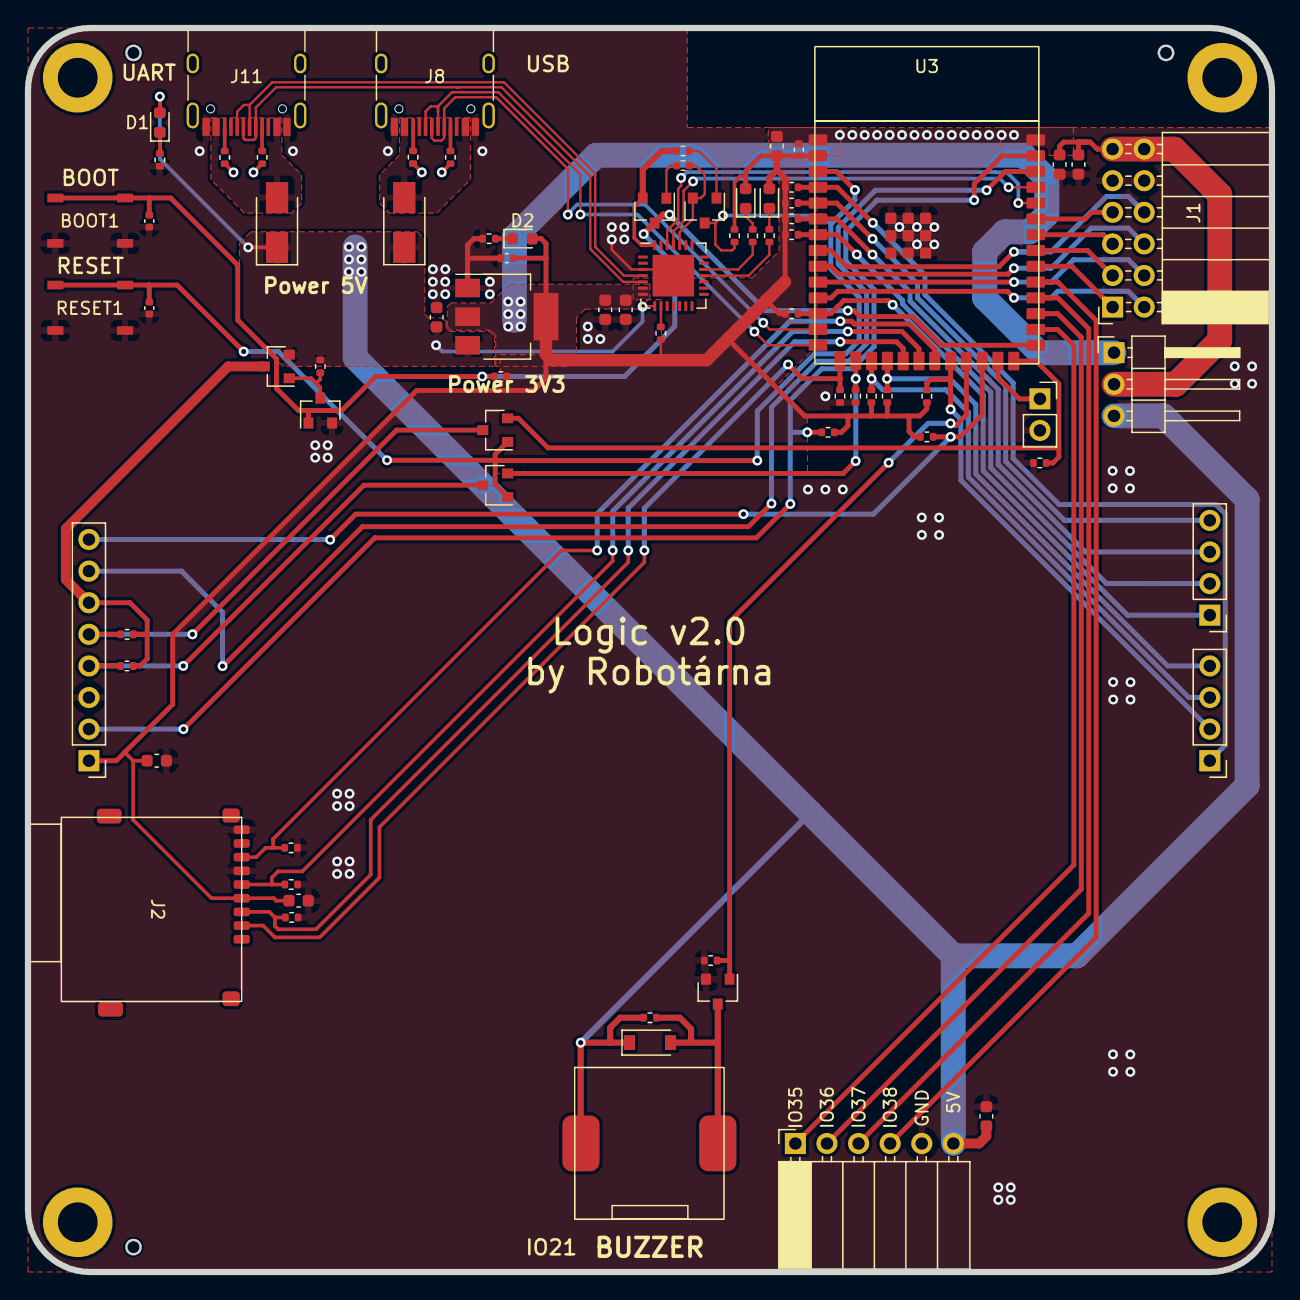
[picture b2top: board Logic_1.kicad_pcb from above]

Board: 2 copper layers, 100.0 x 100.0 mm, 82 parts (0 on the bottom side), 65 nets.

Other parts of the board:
B2: Board
J7: Conn_01x08; PinHeader_1x08_P2.54mm_Vertical
J9, J10: Conn_01x04; PinHeader_1x04_P2.54mm_Vertical

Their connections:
/elektronika.sch/3V3: J7.1; also elsewhere on the board
/elektronika.sch/DATA_HERNI_LED: J7.5; also elsewhere on the board
/elektronika.sch/DATA_ZADANI_LED: J7.4; also elsewhere on the board
/elektronika.sch/GND: J7.3; also elsewhere on the board
/elektronika.sch/SENZOR_SVETLA: J7.7; also elsewhere on the board
/elektronika.sch/SW_2: J10.4; also elsewhere on the board
/elektronika.sch/SW_3: J10.3; also elsewhere on the board
/elektronika.sch/SW_4: J9.4; also elsewhere on the board
/elektronika.sch/SW_5: J9.1; also elsewhere on the board
/elektronika.sch/SW_7: J7.2; also elsewhere on the board
/elektronika.sch/SW_8: J10.2; also elsewhere on the board
/elektronika.sch/SW_9: J9.2; also elsewhere on the board
/elektronika.sch/SW_10: J9.3; also elsewhere on the board
/elektronika.sch/SW_11: J10.1; also elsewhere on the board
/elektronika.sch/SW_12: J7.8; also elsewhere on the board
/elektronika.sch/V_LED: J7.6; also elsewhere on the board

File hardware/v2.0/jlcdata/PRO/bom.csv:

Comment,Designator,Footprint,LCSC
button,"BOOT1,RESET1",my_library:Tactile_switch,C318887
Buzzer,BZ1,Robotarna_KiCad_Library:PKLCS1212E-(RH-Logic_piezzo),C113159
10uF,"C1,C4,C5,C22,C23,C24,C27,C127,C128",Capacitor_SMD:C_0603_1608Metric,C96446
100n,"C25,C28",Capacitor_SMD:C_0402_1005Metric,C1525
1u,"C26,C29",Capacitor_SMD:C_0402_1005Metric,C52923
green,"D1,D2,D9,D10",LED_SMD:LED_0603_1608Metric,C72043
DIODE,"D7,D8",Diode_SMD:D_SMA,C8678
D_Schottky,D114,Diode_SMD:D_SOD-123,C8598
Conn_02x06_Odd_Even,J1,Connector_PinSocket_2.54mm:PinSocket_2x06_P2.54mm_Horizontal,C2897426
Micro_SD_Card,J2,my_library:TF-01A,C91145
Conn_01x08,J7,Connector_PinHeader_2.54mm:PinHeader_1x08_P2.54mm_Vertical,C124381
USB_C_Receptacle_USB2.0,"J8,J11",Connector_USB:USB_C_Receptacle_HRO_TYPE-C-31-M-12,C165948
Conn_01x04,"J9,J10",Connector_PinHeader_2.54mm:PinHeader_1x04_P2.54mm_Vertical,C124378
Conn_01x03,J13,Connector_PinHeader_2.54mm:PinHeader_1x03_P2.54mm_Horizontal,C2935928
Q_NPN_BEC,"Q1,Q2",Package_TO_SOT_SMD:SOT-23,C20526
Q_NMOS_GSD,"Q4,Q6,Q7,Q8",Package_TO_SOT_SMD:SOT-23,C8545
Q_PMOS_GSD,Q5,Package_TO_SOT_SMD:SOT-23,C15127
10k,"R1,R2,R3,R4,R6,R7,R8,R9,R10,R11,R12,R14,R18,R22,R23,R24,R25,R26,R27,R28,R29,R30,R31,R32,R33,R34,R35,R36",Resistor_SMD:R_0402_1005Metric,C25744
100k,"R15,R19",Resistor_SMD:R_0402_1005Metric,C25741
5k1,"R16,R17,R20,R21",Resistor_SMD:R_0402_1005Metric,C25905
AMS1117-3.3,U1,Package_TO_SOT_SMD:SOT-223-3_TabPin2, C6186
CP2102N-A01-GQFN28,U2,Package_DFN_QFN:QFN-28-1EP_5x5mm_P0.5mm_EP3.35x3.35mm,C6568
ESP32-S3-WROOM,U3,Robotarna_KiCad_Library:ESP32-S3-WROOM,C2913199

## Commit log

2022-02-17 v1.1 for RoboCamp 2021
2022-02-17 deleted connector J2, changed location of switches SW7, 9, 10, 11, add library, change procesor - ESP32-WROVER,
2022-08-24 Start v1.1-RH revision
2022-08-25 Final touch for the RH version
2022-08-25 Fix LED correction
2022-09-06 Add basic web structure
2022-09-06 Create CNAME
2022-09-13 First draft of the translation
2022-09-15 Proofread
2022-09-15 Make sure CNAME is not lost on force-push to gh-pages
2022-09-15 Add camp and GH links
2022-09-17 Copy readme from folder web to root
2023-02-13 V2.0 ESP32_S3
    - ESP32_S3
    - two digilent connectors
2023-02-15 Secondary button cross
2023-02-17 SD karta and factory files
2023-02-17 Readme
2023-06-12 RH v2 version
2023-06-12 Change piezo
2023-06-20 Add .csv files
2023-07-12 Add docs for 2.0 version
2023-07-12 Fix deploy
2023-07-13 Add new images of logic
2023-07-13 Add PMOD, SDCard, HW changelog
2023-07-13 Fix typo
2023-07-13 Fix typos
2023-07-14 Migrate to logic.robotikabrno.cz
2023-07-14 Add czech localization for root page
2023-12-05 Microphone and a few minor changes
2024-03-11 Move C22 away from the SD card
2024-03-11 Small tidy up
2024-03-11 Deployed 0aa4b6a with MkDocs version: 1.4.3
2024-09-09 Fix PMOD conectors
2024-09-10 Connector labels
2024-09-10 Deployed 9ed624d with MkDocs version: 1.4.3
2025-02-23 Add czech version of the updated docs
2025-02-23 Add language switcher
2025-02-23 Deployed 95bfc66 with MkDocs version: 1.5.3
